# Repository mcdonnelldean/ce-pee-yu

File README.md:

# Cee Pee Yu

Cee Pee Yu is a Modular PCB based 8-Bit CPU Study. It follows Ben Eater's, [Build an 8-Bit Computer][], reference design as it's basis.

The primary differentiation is the fact that Cee Pee Yu is not built on a series of bread boards, rather, it is composed of a number of custom designed PCB boards. Besides this, there are minor additions and changes to make the project more compatible with PCB Format.

Go to the site: [cee-pee-yu.mcddv.me][]

[Build an 8-Bit Computer]: https://eater.net/
[cee-pee-yu.mcddv.me]: http://cee-pee-yu.mcddv.me/

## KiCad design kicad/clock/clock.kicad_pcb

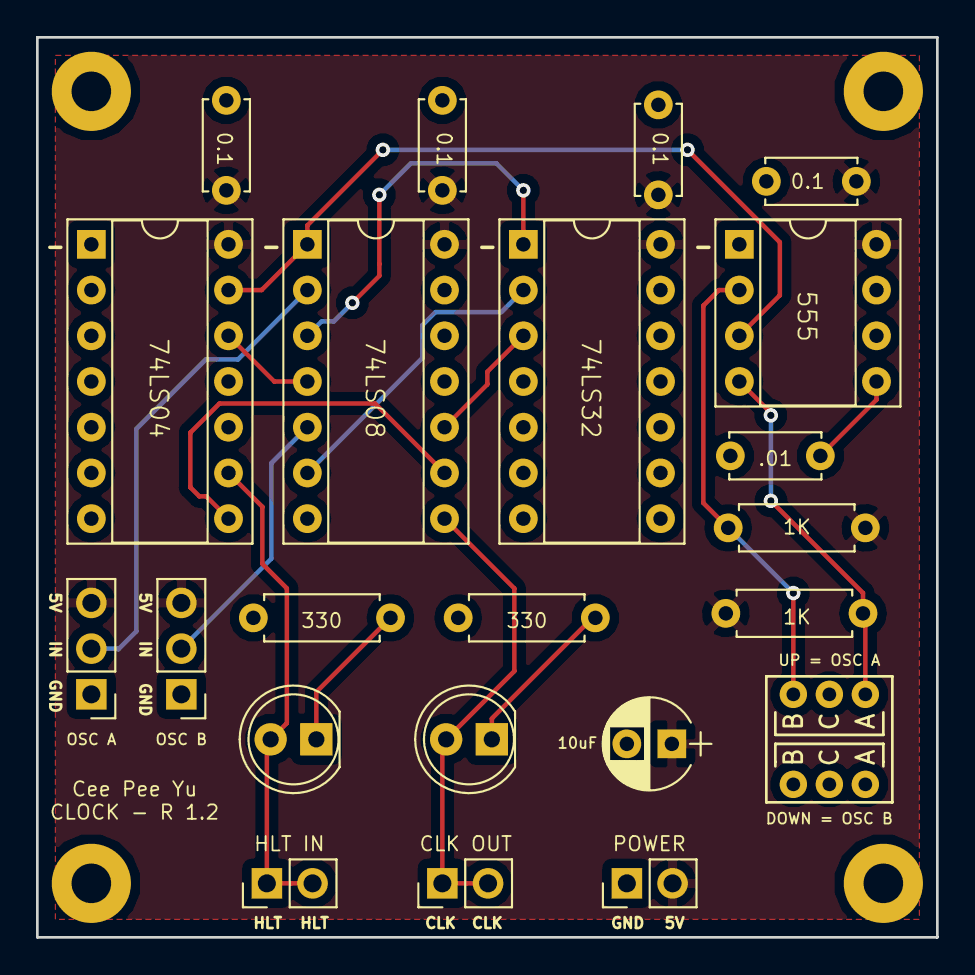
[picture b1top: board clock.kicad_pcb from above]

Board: 2 copper layers, 50.0 x 50.0 mm, 22 parts (0 on the bottom side), 17 nets.

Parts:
C1, C2, C3, C6: 0.1uF; C_Disc_D5.0mm_W2.5mm_P5.00mm
C4: 0.01uF; C_Disc_D5.0mm_W2.5mm_P5.00mm
C5: 10uF; CP_Radial_D5.0mm_P2.50mm
D1, D2: LED; LED_D5.0mm
J1: HLT IN; Socket_Strip_Straight_1x02_Pitch2.54mm
J2: CLK OUT; Socket_Strip_Straight_1x02_Pitch2.54mm
J3: 5v IN; Socket_Strip_Straight_1x02_Pitch2.54mm
J4: OSC A; Socket_Strip_Straight_1x03_Pitch2.54mm
J5: OSC B; Socket_Strip_Straight_1x03_Pitch2.54mm
R1, R2: 330; R_Axial_DIN0207_L6.3mm_D2.5mm_P7.62mm_Horizontal
R3, R4: 1K; R_Axial_DIN0207_L6.3mm_D2.5mm_P7.62mm_Horizontal
SW1: SEL SW; SW_DPDT_L7mm_P2mm
U1: 74LS04; DIP-14_W7.62mm_Socket
U2: 74LS08; DIP-14_W7.62mm_Socket
U3: 74LS32; DIP-14_W7.62mm_Socket
U4: LM555; DIP-8_W7.62mm_Socket

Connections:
/HLT: D1.2, J1.1, J1.2, U1.9
/OSC_A: J4.2, U2.2
/OSC_B: J5.2, U2.5
/OUT: D2.2, J2.1, J2.2, U2.8
/SEL: U1.13, U2.1, U4.3
GND: C1.1, C2.1, C3.1, C4.2, C5.2, C6.2, J3.1, J4.1, J5.1, R1.1, R2.2, SW1.2, U1.7, U2.7, U3.7, U4.1, U4.6
unnamed: C4.1, U4.5
unnamed: D1.1, R1.2
unnamed: D2.1, R2.1
unnamed: R3.2, SW1.3, U4.2
unnamed: R4.2, SW1.1, U4.4
unnamed: U1.8, U2.9
unnamed: U1.12, U2.4
unnamed: U2.3, U3.1
unnamed: U2.6, U3.2
unnamed: U2.10, U3.3
VCC: C1.2, C2.2, C3.2, C5.1, C6.1, J3.2, J4.3, J5.3, R3.1, R4.1, U1.14, U2.14, U3.14, U4.8

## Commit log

2018-08-08 Adds docsify based index.hmtl
2018-08-08 Create CNAME
2018-08-08 Various, - complete rename - add sidebar for testing
2018-08-08 Rebase nits
2018-08-10 Add some pages (#3)
    * Create introduction.md
    * Update sidebar.md
2018-08-10 Add initial readme content
2018-08-10 Update Readme Name
2018-08-11 Push latest
2018-08-11 Clock first pass
2018-08-12 Add clock schematic
2018-08-12 Update CNAME
2018-08-12 fix sidebar
2018-08-12 fix sidebar (#4)
2018-08-13 Add image zoom
2018-08-13 fix sidebar (#5)
2018-08-13 Tell GH not to try process as a jeykll site
2018-08-13 Rename README.md to guide/README.md
2018-08-13 Add pcb first pass for clock (#6)
2018-08-13 Add pcb first pass for clock
2018-08-14 Cleanup old docs
2018-08-14 Clock pcb (#7)
    * Add pcb first pass for clock
    * Cleanup old docs
2018-08-17 More info on clock, plus gerbers
2018-08-17 Clock pcb (#8)
    * Cleanup old docs
    * More info on clock, plus gerbers
2018-08-18 first pass at osc-a
2018-08-18 Inital osc-b schematic
2018-08-18 Added Power / Signal bus sch
2018-08-18 Add bus indicator schematic
2018-08-18 Add schematics for everything up to bus (#9)
    * first pass at osc-a
    * Inital osc-b schematic
    * Added Power / Signal bus sch
    * Add bus indicator schematic
2018-12-13 Update files
